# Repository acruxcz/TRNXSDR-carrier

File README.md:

# #TRNXSDR - Open RF Research Platform

**A modular baseboard designed for advanced Software Defined Radio (SDR) ecosystems.**

---

## 📝 Project Overview
The **TRNXSDR** is a hardware platform engineered to host and interconnect specialized SDR modules. It acts as the central processing hub, providing high-speed logic, memory bandwidth, and versatile connectivity for complex radio applications.

> [!IMPORTANT]
> The **TRNXSDR** is a **Baseboard Platform**. While it provides the processing power and RF routing, it requires external SDR modules connected via the expansion slots for full radio functionality.

## #TRNXSDR Baseboard

---

## Key Technical Specifications

### ⚙️ Processing & Memory
*   **FPGA XC7Z015 Core**: High-speed logic for real-time Digital Signal Processing (DSP).
*   **1 GB DDR3 RAM @ 1066 MHz**: High-capacity memory for data buffering and complex waveform processing.
*   **80-pin Module Connectors**: High-density connectors ensuring reliable signal integrity between the baseboard and modules.

### 🌐 Connectivity & I/O
*   **1 Gbit Ethernet (Copper)**: Standard high-speed network integration.
*   **Optical Ethernet (SFP)**: Hardware ready for fiber-optic connection. Planned support for **1 Gbit / 2.5 Gbit+** throughput via GTX connection (up to **5 Gbit** for custom digital IF).
*   **USB-C**: Hardware support for **Power Delivery (PD)** to power the entire board via a single cable (9–20 V input). Firmware currently under development.
*   **4 SMA RF Connectors**: On-board SMA connectors for direct and stable antenna connections.

---

## 🛠 Modular Ecosystem & Scalability
The platform is designed to grow. The baseboard features a flexible slot system to accommodate various SDR modules.

| Slot Type | Quantity | Technical Capabilities |
| :--- | :---: | :--- |
| **Primary HS Slots** | **2** | **High-Speed Support**: 1x with 2L GTX (JESD204B support), both slots support LVDS. |
| **Primary LS Slots** | **2** | **Standard I/O**: Optimized for general-purpose SDR control and low-speed buses. |
| **Expansion Board** | **+6** | **Low-Speed Expansion**: Optimized for SPI, I2C, and LVDS control buses. |

---

## 💻 Software & Integration

### GNU Radio Support (Active Development)
**Core functionality is already verified!** We have developed a custom **OOT (Out-Of-Tree) Module**, enabling basic RX streaming between the hardware and GNU Radio.
*   *Current focus*: Stability improvements, feature expansion, and bug fixes.

Below, you can see a GNU Radio Companion (GRC) flowgraph demonstrating the implementation of the dedicated #TRNXSDR source block.

### Signal Analysis & Verification
To verify the RF chain's integrity, we tested the SDR in the 433 MHz band. The following image shows the captured spectrum in GRC, displaying a clean signal peak and minimal noise floor.

Furthermore, we performed a dynamic frequency shift test. In the waterfall plot below, you can see a "snake" pattern created by manually sweeping the carrier frequency. The sweep was performed roughly within a ±500 kHz range around the 433 MHz center.

### Future Software Roadmap (Planned)
*   **SoapySDR Compatibility**: Integration of a SoapySDR driver to provide a vendor-neutral API for tools like **SDR++, SDRangel, GNU Radio and more**.
*   **OpenWiFi Project**: Investigating the possibility of hosting the OpenWiFi stack (IEEE 802.11 FPGA/Software) on #TRNXSDR hardware.

---

## #TRNXSDR with AT86RF215 SDR Module and RFFC5072 Mixer Module + RF Front-End (LNA, PA...) Module

---

## 🟢 Future Hardware Roadmap
Expanding the #TRNXSDR ecosystem with high-end RF modules:
*   **Expansion Board**: A dedicated add-on board adding **6 additional low-speed slots** (Total of 10 modules).
*   **New SDR Modules**:
    *   **Lime Ecosystem**: Modules based on **LMS6002D** and **LMS7002M** (MIMO, wide frequency range).
    *   **Analog Devices Series**: High-performance transceivers based on **AD9361 / AD9363 / AD9364**.

---

## 🛠 Development Status

- [x] **Baseboard Hardware Design**: Completed (Rev 1.0) — *Functional, with known bugs being addressed.*
- [/] **Hardware Revision 2.0**: In progress (bug fixes and optimizations).
- [/] **GNU Radio OOT Module**: Functional — *Ongoing development and feature updates.*
- [/] **Optical Port**: Hardware ready, firmware development in progress.
- [/] **USB-C Power Delivery**: Hardware support implemented, firmware under active development.
- [ ] **SoapySDR & OpenWiFi**: Conceptual/Planned stage.

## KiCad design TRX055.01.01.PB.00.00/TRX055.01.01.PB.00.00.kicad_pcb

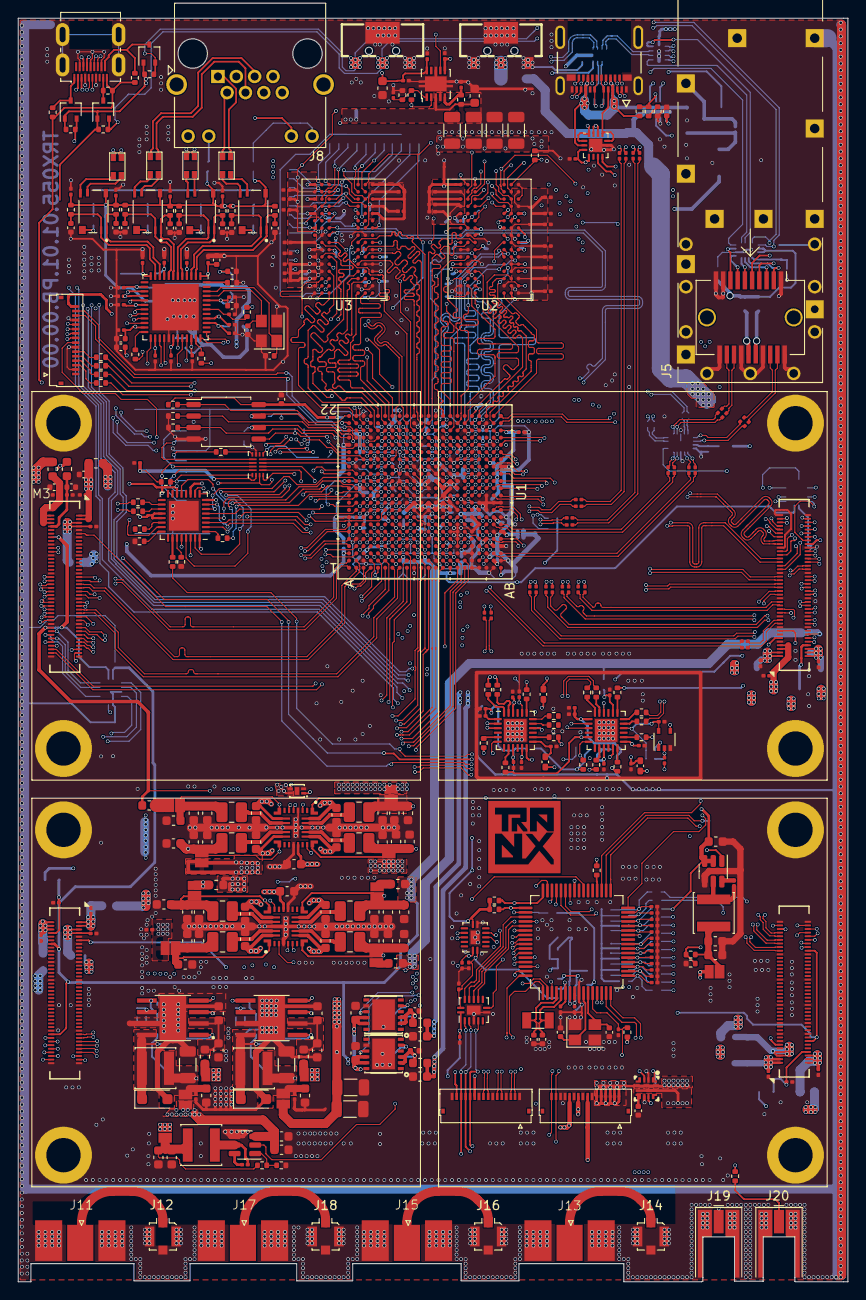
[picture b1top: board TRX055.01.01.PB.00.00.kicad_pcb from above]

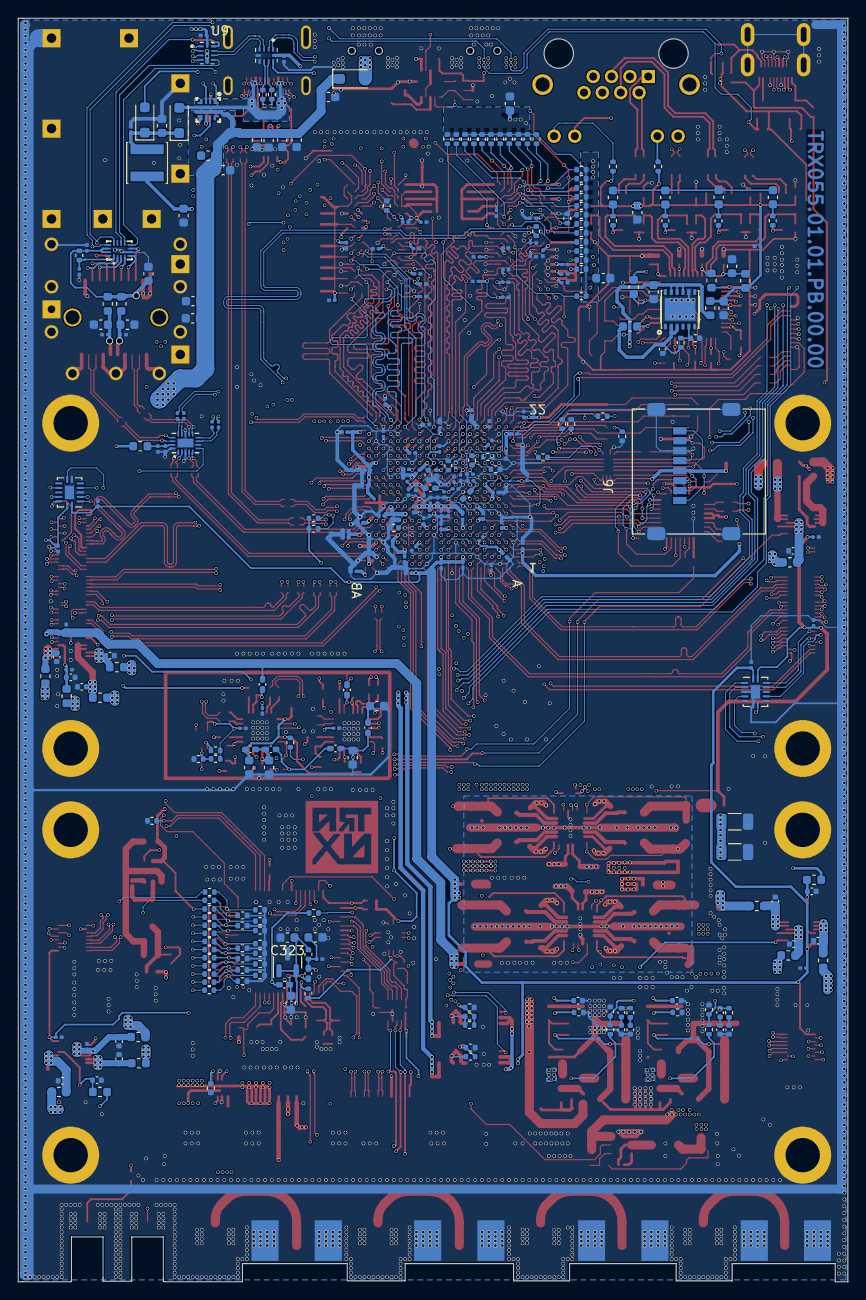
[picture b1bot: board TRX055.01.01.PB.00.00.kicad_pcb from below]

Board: 6 copper layers, 91.8 x 139.8 mm, 702 parts (313 on the bottom side), 611 nets.

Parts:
C1, C2, C3, C4, C5, C6, C7, C8, C9, C10, C11, C12, C13, C14, C15, C16, C17, C18, C19, C20, C21, C22, C23, C24, C111, C148, C149, C150, C154, C155, C156, C157, C158, C159, C160, C161, C162, C163, C164, C165, C169, C171, C174, C176, C227, C229, C231, C233, C234, C239, C245, C246, C247, C248, C249, C250, C257, C282, C283, C284, C285, C286, C288, C310, C311, C313, C314, C323, C324, C325, C326: 10M; C_0603_1608Metric
C25, C113, C114, C117, C124, C127, C186, C188, C190, C192, C194, C196, C198, C200, C202, C204, C206, C208, C210, C212, C214, C216, C240, C244, C289: 1M; C_0402_1005Metric
C26, C27, C28, C29, C30, C31, C32, C33, C34, C35, C36, C37, C38, C39, C40, C41, C42, C43, C44, C45, C46, C47, C48, C49, C50, C51, C52, C53, C54, C55, C56, C57, C58, C59, C60, C61, C62, C63, C64, C65, C66, C67, C68, C69, C70, C71, C72, C73, C74, C75, C76, C77, C78, C79, C80, C81, C82, C83, C84, C85, C86, C87, C88, C89, C90, C91, C92, C93, C94, C95, C96, C97, C98, C99, C100, C101, C102, C103, C104, C105, C106, C107, C110, C112, C115, C116, C118, C119, C120, C121, C122, C123, C125, C126, C128, C129, C130, C133, C137, C141, C145, C147, C151, C152, C153, C166, C167, C168, C170, C172, C173, C175, C177, C178, C179, C184, C185, C187, C189, C191, C193, C195, C197, C199, C201, C203, C205, C207, C209, C211, C213, C215, C217, C218, C219, C220, C221, C222, C223, C224, C225, C226, C228, C230, C232, C235, C236, C253, C258, C259, C260, C261, C262, C263, C264, C265, C266, C267, C268, C269, C270, C271, C272, C273, C274, C275, C276, C277, C278, C281, C287, C290, C291, C292, C293, C294, C295, C296, C297, C298, C299, C300, C301, C302, C303, C304, C305, C306, C307, C308, C309, C312, C315, C316, C317, C318, C319, C320, C321, C322, C327, C328, C329, C330, C331, C332, C333, C334, C335, C336, C337, C338, C339, C340, C341, C342, C343, C344, C345, C346, C347, C348, C349, C350, C351, C352, C353, C354, C355, C356, C357, C358, C359, C360, C361, C362, C363, C364, C365, C366, C367, C368, C382, C383: M1; C_0201_0603Metric
C108, C109, C131, C132, C135, C136, C139, C140, C143, C144, C180, C181, C182, C183, C237, C241, C243, C252, C254, C255: 10P; C_0402_1005Metric
C134, C138, C142, C146: 1N; C_0603_1608Metric
C238, C256, C378, C379, C380, C381, C391, C395, C396, C397: 100M; C_1206_3216Metric
C242, C251: 10N (DNP); C_0402_1005Metric
C279, C280: Cap; C_0402_1005Metric
C369, C370, C371, C372, C373, C374, C375, C376, C377: 22M; C_0603_1608Metric
D1, D2, D3, D4, D5: DSK34; D_SOD-123F
FB1, FB2, FB3, FB4, FB5, FB7, FB8, FB9, FB10, FB18, FB19, FB20, FB21, FB22, FB23, FB24, FB25, FB26, FB27, FB28, FB29, FB30, FB31, FB32, FB33, FB34, FB35, FB36, FB37, FB38, FB39, FB40: BLM18PG330SN1D; L_0603_1608Metric
FB6, FB11, FB12, FB13, FB14, FB15, FB16, FB17, FB41, FB42, FB43, FB44, FB45: GZ1005U102TF; L_0402_1005Metric_Pad0.77x0.64mm_HandSolder
J5: SFP; Connector_SFP_and_Cage
J6: Micro_SD_Card; microSD_HC_Molex_47219-2001
J7: HDMI_D_1.4; HDMI_Micro-D_Molex_46765-1x01
J8: RJHSE5383; RJ45_Amphenol_RJHSE538X
J9: 1054500101; MOLEX_1054500101
J10, J23, J24: Conn_01x16_Pin; FH34SRJ-16S-0.5SH
J11, J13, J15, J17: HYCW12-SMAW0863-1365B; sma-edge
J12, J14, J16, J18: U.FL-R-SMT-1(80); U.FL_Molex_MCRF_73412-0110_Vertical
J19, J20: Conn_Coaxial; MMCX_Molex_73415-0961_Horizontal_1.6mm-PCB
J21, J22: GT-BTP30003-0720A-016A; BAT-SMD_GT-BTP30003-0500A-016A-1
JP1, JP2, JP3, JP4, JP5, JP6, JP7, JP8, JP9, JP10, JP11, JP12, JP13, JP14: Jumper_2_Open; SolderJumper-2_P1.3mm_open_Pad1.0x1.5mm
L1, L2, L3, L4, L5, L6, L7, L8: DFE252012PD-R47M; L_1008_2520Metric
L9, L10, L11, L12: SRF2012A-801Y
L13, L15, L16, L17, L18: EXLA1V0402-4R7-R; EXLA1V04
M1, M2, M3, M4: DF40HC-80DS; module_sdr_kit_base
Q1, Q2, Q3: NTS4001NT1G; SOT-323_SC-70
R1, R2, R3, R4, R6, R8, R12, R49, R69, R70, R71, R72, R86, R88, R89, R91, R92, R93, R94, R95, R96, R97, R101, R102, R103, R104, R105, R106, R107, R108, R109, R110, R111, R112, R113, R114, R115, R116, R117, R118, R119, R120, R121, R122, R123, R124, R125, R126, R127, R128, R130, R131, R132, R133, R134, R135, R136, R142, R143, R146, R147, R148, R149, R150, R151, R153, R154, R155, R156, R157, R158, R159, R160, R161, R164, R165, R166: 10K; R_0402_1005Metric
R5, R7, R162: 5K1; R_0402_1005Metric
R9, R10, R11, R13, R15, R16, R30, R31, R32, R33, R34, R35, R36, R37, R38, R39, R40, R41, R42, R43, R44, R45, R46, R47: 39R; R_0402_1005Metric
R14, R17, R18, R19, R20, R21, R22, R23, R24, R25, R26, R27, R28, R56, R57, R73, R74, R75, R76, R77, R78, R79, R80, R81, R82, R83, R84, R85, R87, R90, R141, R144, R145, R163: 33R; R_0402_1005Metric
R29, R98: 8K06; R_0402_1005Metric
R48, R52, R53: 80R; R_0402_1005Metric
R50, R51: 240R; R_0402_1005Metric
R54: 12K1; R_0402_1005Metric
R55, R58, R60, R61, R63, R64, R66, R67: 49R9; R_0402_1005Metric
R59, R62, R65, R68: 75R; R_0402_1005Metric
R99, R100: 240; R_0402_1005Metric
R129: 100K; R_0402_1005Metric
R137, R139: 33; R_0402_1005Metric
R138, R140: NU; R_0402_1005Metric
R152: 500; R_0402_1005Metric
T1, T2, T3, T4: SM453229-231N7Y; XFMR_SM453229-231N7Y
U1: XC7Z015-2CLG485I; CLG485XC7Z012S&slash_XC7Z015_AMD
U2, U3: K4B4G1646E-BYMA; BGA-96_9.0x13.0mm_Layout2x3x16_P0.8mm
U4, U6: LP87524JRNFRQ1; VREG_LP87524JRNFRQ1
U5, U8, U31: NCP186AMN080TBG; DFN-12_L4.0-W4.0-P0.65-BL-EP3.4
U7, U34: TPS54531DDAR; CONV_TPS54531DDAR
U9, U20: TS3USB221RSER; IC_TPD6E001RSER
U10: NVT4858HKZ; XQFN16
U11: KSZ9031RNXCA; QFN-48-1EP_7x7mm_P0.5mm_EP5.15x5.15mm
U12: USB3320C-EZK-TR; QFN-32-1EP_5x5mm_P0.5mm_EP3.3x3.3mm
U13, U16: 5P35023B-000NLGI; VQFN-24-1EP_4x4mm_P0.5mm_EP2.5x2.5mm
U14: W25Q128JVSIQ; SOIC-8_5.23x5.23mm_P1.27mm
U15: TPS51200DRC; VSON-10-1EP_3x3mm_P0.5mm_EP1.65x2.4mm
U17: STM32G070RBTx; LQFP-64_10x10mm_P0.5mm
U18: TL431DBZ; SOT-23
U19, U23, U32, U33: TXU0304; DHVQFN-14-1EP_2.5x3mm_P0.5mm_EP1x1.5mm
U21, U30: AP63203WU; TSOT-23-6
U22: TCA6408ARSVR; UQFN-16_L2.6-W1.8-P0.40-BL
U24: SIP32409DNP-T1-GE4; UDFN-5_L1.6-W1.2-P0.50-BL-EP
U25: FUSB302BMPX; WQFN-14-1EP_2.5x2.5mm_P0.5mm_EP1.45x1.45mm
U26: FUSB340TMX; TMLP-18_L2.8-W2.0-P0.40-BL-EP
U27, U29: LM73100RPWR; VQFN-10_L2.0-W2.0-P0.45-TL
U28: SN74LVC1G125DCKR; SOT-353_SC-70-5
Y1, Y2: X322525MOB4SI; Crystal_SMD_3225-4Pin_3.2x2.5mm
Y3: XKXGI-SUA-32.768K; Crystal_SMD_3215-2Pin_3.2x1.5mm

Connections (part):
+1V2: C244.1, FB37.1, R5.1, U8.2 (OUT), U8.3 (OUT)
+1V8: C25.1, C26.1, C27.1, C57.1, C58.1, C59.1, C60.1, C127.1, C128.1, C129.1, C130.1, C247.1, C248.1, C293.1, FB6.1, FB43.2, J10.16, JP4.2 (B), R12.1, R69.1, R146.2, R151.2, R153.2, R155.2, R156.2, R157.1, R158.1, U1.A13 (VCCO_MIO1_501), U1.B10 (VCCO_MIO1_501), U1.B20 (VCCO_MIO0_500), U1.C17 (VCCO_MIO0_500), U1.D14 (VCCO_MIO1_501), U1.E11 (VCCO_MIO1_501), U1.K14 (VCCPAUX), U1.L13 (VCCPAUX), U1.M14 (VCCPAUX), U1.P14 (VCCPAUX), U1.R11 (VCCO_0), U5.10 (IN), U5.11 (IN), U8.10 (IN), U8.11 (IN), U10.15 (VCCA), U11.16 (DVDDH), U11.34 (DVDDH), U11.40 (DVDDH), U12.8 (REFSEL0), U12.11 (REFSEL1), U12.14 (REFSEL2), U12.28 (VDD18), U12.30 (VDD18), U12.32 (VDDIO), U14.8 (VCC), U24.1 (IN), U33.8 (OE), U33.14 (VCCB)
+3V3: C153.1, C154.1, C226.1, C231.1, C232.1, C273.1, C275.2, C276.2, C277.2, C278.2, C288.1, FB4.2, FB34.2, FB35.2, FB40.2, FB42.2, J6.4 (VDD), JP7.2 (B), Q1.1 (G), Q2.1 (G), Q3.1 (G), R95.1, R103.1, R104.1, R106.1, R154.2, U9.10 (VCC), U10.14 (VCCB), U12.20 (VDD33), U12.21 (VBAT), U12.23 (ID), U15.10 (VIN), U20.10 (VCC), U22.14 (VCCP), U22.15 (VCCI), U25.3 (VDD), U25.4 (VDD), U31.9 (EN), U31.10 (IN), U31.11 (IN)
/A1_HS1_CLK_N: M1.22, U1.AA14 (IO_L11P_T1_SRCC_13)
/A1_HS1_CLK_P: M1.20, U1.AA15 (IO_L11N_T1_SRCC_13)
/A1_HS_4_N: M1.36, U1.AA11 (IO_L7P_T1_13)
/A1_HS_4_P: M1.38, U1.AB11 (IO_L7N_T1_13)
/A1_HS_5_N: M1.35, U1.V11 (IO_L4P_T0_13)
/A1_HS_5_P: M1.37, U1.W11 (IO_L4N_T0_13)
/A1_HS_6_N: M1.40, U1.W12 (IO_L3P_T0_DQS_13)
/A1_HS_6_P: M1.42, U1.W13 (IO_L3N_T0_DQS_13)
/A1_HS_7_N: M1.39, U1.AB12 (IO_L8N_T1_13)
/A1_HS_7_P: M1.41, U1.AA12 (IO_L8P_T1_13)
/A1_HS_8_N: M1.44, U1.AB13 (IO_L9P_T1_DQS_13)
/A1_HS_8_P: M1.46, U1.AB14 (IO_L9N_T1_DQS_13)
/A1_HS_9_N: M1.43, U1.Y12 (IO_L10P_T1_13)
/A1_HS_9_P: M1.45, U1.Y13 (IO_L10N_T1_13)
/A1_HS_10_N: M1.50, U1.V15 (IO_L2P_T0_13)
/A1_HS_10_P: M1.52, U1.W15 (IO_L2N_T0_13)
/A1_HS_11_N: M1.49, U1.AA17 (IO_L14N_T2_SRCC_13)
/A1_HS_11_P: M1.51, U1.AA16 (IO_L14P_T2_SRCC_13)
/A1_HS_12_N: M1.54, U1.V16 (IO_L23P_T3_13)
/A1_HS_12_P: M1.56, U1.W16 (IO_L23N_T3_13)
/A1_HS_13_N: M1.53, U1.W17 (IO_L24P_T3_13)
/A1_HS_13_P: M1.55, U1.Y17 (IO_L24N_T3_13)
/A1_HS_14_N: M1.58, U1.AB16 (IO_L17P_T2_13)
/A1_HS_14_P: M1.60, U1.AB17 (IO_L17N_T2_13)
/A1_HS_15_N: M1.57, U1.AB21 (IO_L15P_T2_DQS_13)
/A1_HS_15_P: M1.59, U1.AB22 (IO_L15N_T2_DQS_13)
/A1_HS_16_N: M1.65, U1.AB19 (IO_L16N_T2_13)
/A1_HS_16_P: M1.63, U1.AB18 (IO_L16P_T2_13)
/A1_HS_17_N: M1.69, U1.AA20 (IO_L18N_T2_13)
/A1_HS_17_P: M1.67, U1.AA19 (IO_L18P_T2_13)
/A1_HS_18_N: M1.73, U1.V19 (IO_L20N_T3_13)
/A1_HS_18_P: M1.71, U1.U19 (IO_L20P_T3_13)
/A1_LS_GPIO_0: M1.72, U1.U12 (IO_L5N_T0_13)
/A1_LS_GPIO_1: M1.74, U1.V14 (IO_L1N_T0_13)
/A1_LS_GPIO_2: M1.76, U1.T16 (IO_0_13)
/A1_LS_GPIO_3: M1.78, U1.U16 (IO_25_13)
/A1_SPI_EN: U1.M8 (IO_L6P_T0_34), U19.8 (OE)
/A2_HS_16_N: M2.65, U1.R3 (IO_L17P_T2_34)
/A2_HS_16_P: M2.63, U1.R2 (IO_L17N_T2_34)
/A2_HS_17_N: M2.69, U1.R5 (IO_L23P_T3_34)
/A2_HS_17_P: M2.67, U1.R4 (IO_L23N_T3_34)
/A2_HS_18_N: M2.73, U1.R7 (IO_L24N_T3_34)
/A2_HS_18_P: M2.71, U1.P7 (IO_L24P_T3_34)
/A2_LS_GPIO_0: M2.72, U1.J7 (IO_L2P_T0_34)
/A2_LS_GPIO_1: M2.74, U1.N6 (IO_L19P_T3_34)
/A2_LS_GPIO_2: M2.76, U1.N5 (IO_L19N_T3_VREF_34)
/A2_LS_GPIO_3: M2.78, U1.P6 (IO_L20P_T3_34)
/A3_HS1_CLK_N: M3.22, U1.C6 (IO_L11P_T1_SRCC_35)
/A3_HS1_CLK_P: M3.20, U1.C5 (IO_L11N_T1_SRCC_35)
/A3_HS_4_N: M3.36, U1.D5 (IO_L12P_T1_MRCC_35)
/A3_HS_4_P: M3.38, U1.C4 (IO_L12N_T1_MRCC_35)
/A3_HS_5_N: M3.35, U1.E5 (IO_L5N_T0_AD9N_35)
/A3_HS_5_P: M3.37, U1.F5 (IO_L5P_T0_AD9P_35)
/A3_HS_6_N: M3.40, U1.A2 (IO_L15P_T2_DQS_AD12P_35)
/A3_HS_6_P: M3.42, U1.A1 (IO_L15N_T2_DQS_AD12N_35)
/A3_HS_7_N: M3.39, U1.B1 (IO_L18N_T2_AD13N_35)
/A3_HS_7_P: M3.41, U1.B2 (IO_L18P_T2_AD13P_35)
/A3_HS_8_N: M3.44, U1.C1 (IO_L16N_T2_35)
/A3_HS_8_P: M3.46, U1.D1 (IO_L16P_T2_35)
/A3_HS_9_N: M3.43, U1.C3 (IO_L14N_T2_AD4N_SRCC_35)
/A3_HS_9_P: M3.45, U1.D3 (IO_L14P_T2_AD4P_SRCC_35)
/A3_HS_10_N: M3.50, U1.D2 (IO_L17N_T2_AD5N_35)
/A3_HS_10_P: M3.52, U1.E2 (IO_L17P_T2_AD5P_35)
/A3_HS_11_N: M3.49, U1.E4 (IO_L21P_T3_DQS_AD14P_35)
/A3_HS_11_P: M3.51, U1.E3 (IO_L21N_T3_DQS_AD14N_35)
/A3_HS_12_N: M3.54, U1.F1 (IO_L23N_T3_35)
/A3_HS_12_P: M3.56, U1.F2 (IO_L23P_T3_35)
/A3_HS_13_N: M3.53, U1.G1 (IO_L24N_T3_AD15N_35)
/A3_HS_13_P: M3.55, U1.H1 (IO_L24P_T3_AD15P_35)
/A3_HS_14_N: M3.58, U1.F4 (IO_L20N_T3_AD6N_35)
/A3_HS_14_P: M3.60, U1.G4 (IO_L20P_T3_AD6P_35)
/A3_HS_15_N: M3.57, U1.G2 (IO_L22N_T3_AD7N_35)
/A3_HS_15_P: M3.59, U1.G3 (IO_L22P_T3_AD7P_35)
/A3_HS_16_N: M3.65, U1.H4 (IO_L19P_T3_35)
/A3_HS_16_P: M3.63, U1.H3 (IO_L19N_T3_VREF_35)
/A3_HS_17_N: M3.69, U1.G6 (IO_L6P_T0_35)
/A3_HS_17_P: M3.67, U1.F6 (IO_L6N_T0_VREF_35)
/A3_HS_18_N: M3.73, U1.G8 (IO_L4P_T0_35)
/A3_HS_18_P: M3.71, U1.G7 (IO_L4N_T0_35)
/A3_LS_GPIO_0: M3.72, U1.H6 (IO_0_35)
/A3_LS_GPIO_1: M3.74, U1.H5 (IO_25_35)
/A3_LS_GPIO_2: M3.76, U1.D7 (IO_L2P_T0_AD8P_35)
/A3_LS_GPIO_3: M3.78, U1.D6 (IO_L2N_T0_AD8N_35)
/A3_SPI_EN: U1.K8 (IO_L1N_T0_34), U23.8 (OE)
/A4_HS_16_N: M4.65, U1.L2 (IO_L10P_T1_34)
/A4_HS_16_P: M4.63, U1.L1 (IO_L10N_T1_34)
/A4_HS_17_N: M4.69, U1.M2 (IO_L15P_T2_DQS_34)
/A4_HS_17_P: M4.67, U1.M1 (IO_L15N_T2_DQS_34)
/A4_HS_18_N: M4.73, U1.P1 (IO_L16N_T2_34)
/A4_HS_18_P: M4.71, U1.N1 (IO_L16P_T2_34)
/A4_LS_GPIO_0: M4.72, U1.K2 (IO_L9N_T1_DQS_34)
/A4_LS_GPIO_1: M4.74, U1.T2 (IO_L13P_T2_MRCC_34)
/A4_LS_GPIO_2: M4.76, U1.U1 (IO_L14N_T2_SRCC_34)
/A4_LS_GPIO_3: M4.78, U1.U2 (IO_L14P_T2_SRCC_34)
/Clocking/CLK_PWR: FB13.1, FB14.1, R142.1
/Clocking/CLK_PWR_VBAT: R142.2, U13.6 (VBAT), U16.6 (VBAT)
/Clocking/CLK_REF_IN: R87.2, R90.2
/Clocking/EXT_REF_EN: R166.2, U17.41 (PD9), U28.1
/Clocking/VDD_13F: C319.1, FB44.1, U13.20 (VDDSE3)
/Clocking/VDD_18F: C318.1, FB43.1, U16.13 (VDDSE1)
/Clocking/VDD_34F: C317.1, C320.1, FB41.1, U13.13 (VDDSE1), U16.20 (VDDSE3)
/Clocking/VDD_35F: C321.1, FB45.1, U13.11 (VDDSE2)
/Clocking/VDD_DIFF: C308.1, C309.1, C315.1, C316.1, C322.1, C383.2, FB42.1, R165.1, R166.1, U13.16 (VDDDIFF1), U13.22 (VDDDIFF2), U16.11 (VDDSE2), U16.16 (VDDDIFF1), U16.22 (VDDDIFF2), U28.5 (VCC)
/ETH_PHY_Metal/ETH_Pair1/MDI_IN_N: C135.1, R60.2, T2.2, U11.8 (TXRXM_C)
/ETH_PHY_Metal/ETH_Pair1/MDI_IN_P: C136.1, R61.2, T2.1, U11.7 (TXRXP_C)
/ETH_PHY_Metal/ETH_Pair1/MDI_N: J8.5, L10.2
/ETH_PHY_Metal/ETH_Pair1/MDI_P: J8.4, L10.3
/ETH_PHY_Metal/ETH_Pair1/POE: R62.1, T2.3, T2.4
/ETH_PHY_Metal/ETH_Pair2/MDI_IN_N: C139.1, R63.2, T3.2, U11.6 (TXRXM_B)
/ETH_PHY_Metal/ETH_Pair2/MDI_IN_P: C140.1, R64.2, T3.1, U11.5 (TXRXP_B)
/ETH_PHY_Metal/ETH_Pair2/MDI_N: J8.6, L11.2
/ETH_PHY_Metal/ETH_Pair2/MDI_P: J8.3, L11.3
/ETH_PHY_Metal/ETH_Pair2/POE: R65.1, T3.3, T3.4
/ETH_PHY_Metal/ETH_Pair3/MDI_IN_N: C143.1, R66.2, T4.2, U11.3 (TXRXM_A)
/ETH_PHY_Metal/ETH_Pair3/MDI_IN_P: C144.1, R67.2, T4.1, U11.2 (TXRXP_A)
/ETH_PHY_Metal/ETH_Pair3/MDI_N: J8.2, L12.2
/ETH_PHY_Metal/ETH_Pair3/MDI_P: J8.1, L12.3
/ETH_PHY_Metal/ETH_Pair3/POE: R68.1, T4.3, T4.4
/ETH_PHY_Metal/ETH_Pair/MDI_IN_N: C131.1, R55.2, T1.2, U11.11 (TXRXM_D)
/ETH_PHY_Metal/ETH_Pair/MDI_IN_P: C132.1, R58.2, T1.1, U11.10 (TXRXP_D)
/ETH_PHY_Metal/ETH_Pair/MDI_N: J8.8, L9.2
/ETH_PHY_Metal/ETH_Pair/MDI_P: J8.7, L9.3
/ETH_PHY_Metal/ETH_Pair/POE: R59.1, T1.3, T1.4
/ETH_PHY_Metal/SMI_MDC: U1.D13 (PS_MIO52_501), U11.36 (MDC)
/ETH_PHY_Metal/SMI_MDIO: U1.C11 (PS_MIO53_501), U11.37 (MDIO)
/ETH_PHY_Metal/nLED1: J8.11, U11.17 (LED1/PHAD0/PME_N1)
/ETH_PHY_Metal/nLED2: J8.9, U11.15 (LED2/PHYAD1)
/EXTIO_CLK_N: J23.9, U1.L4 (IO_L12N_T1_MRCC_34)
/EXTIO_CLK_P: J23.8, U1.L5 (IO_L12P_T1_MRCC_34)
/EXTIO_CS: J23.15, U1.K5 (IO_L7N_T1_34)
/EXTIO_D0_N: J23.6, U1.N3 (IO_L21N_T3_DQS_34)
/EXTIO_D0_P: J23.5, U1.N4 (IO_L21P_T3_DQS_34)
/EXTIO_D1_N: J23.3, U1.P2 (IO_L18N_T2_34)
/EXTIO_D1_P: J23.2, U1.P3 (IO_L18P_T2_34)
/FCCLK: U4.3 (CLKIN), U6.3 (CLKIN), U17.39 (PC7)
/FPGA_CLK_REF_0: R77.2, R163.2, U1.T1 (IO_L13N_T2_MRCC_34), U13.5 (CLKINB/X1)
/FPGA_CLK_REF_1_N: R78.2, U1.K3 (IO_L11N_T1_SRCC_34)
/FPGA_CLK_REF_1_P: R79.2, U1.K4 (IO_L11P_T1_SRCC_34)
/GTP_REF_CLK0_N: C106.1, M1.21
/GTP_REF_CLK0_P: C104.1, M1.19
/GTP_REF_CLK1_N: C105.1, R22.2
/GTP_REF_CLK1_P: C107.1, R23.2
/GT_LANE0_SEL: U17.35 (PB15), U26.6 (S)
/GT_RX0_N: C91.1, U26.5 (SSRXCOM+)
/GT_RX0_P: C90.1, U26.4 (SSRXCOM-)
/GT_RX1_N: C89.1, C269.1
/GT_RX1_P: C88.1, C270.1
/GT_RX2_N: C93.1, M1.29
/GT_RX2_P: C92.1, M1.31
/GT_RX3_N: C95.1, M1.30
/GT_RX3_P: C94.1, M1.32
/GT_TX0_N: C97.1, U26.2 (SSTXCOM+)
/GT_TX0_P: C96.1, U26.1 (SSTXCOM-)
/GT_TX1_N: C98.1, C268.1
/GT_TX1_P: C99.1, C267.1
/GT_TX2_N: C100.1, M1.25
/GT_TX2_P: C101.1, M1.27
/GT_TX3_N: C102.1, M1.26
/GT_TX3_P: C103.1, M1.28
/HDMI/HDMI_HPD: Q3.2 (S), R106.2, U17.59 (PB5)
/MOD_A1_REFCLK: M1.11, R82.2
/MOD_A2_REFCLK: M2.11, R84.2
/MOD_A3_REFCLK: M3.11, R83.2
/MOD_A4_REFCLK: M4.11, R74.2
/Main_Power/BOOT_PWR: C286.1, C287.2, D1.1 (K), D5.1 (K), L16.1
/Main_Power/OVLO: R98.1, R99.1, U27.2 (OVLO)
/Main_Power/TPS5430DD_DCDC1/FB: R93.2, R94.1, U7.5 (VSENSE)
/Main_Power/TPS5430DD_DCDC1/TPSSW: C253.2, D3.1 (K), L13.1, U7.8 (PH)
/Main_Power/TPS5430DD_DCDC1/TPSVIN: C249.1, C250.1, FB39.2, U7.2 (VIN)
/Main_Power/TPS5430DD_DCDC1/TPSVOUT: C256.1, C257.1, C258.1, JP12.1 (A), L13.2, R93.1
/Main_Power/TPS5430DD_DCDC1/VIN: FB39.1, JP11.2 (B)
/Main_Power/TPS5430DD_DCDC/FB: R2.2, R3.1, U34.5 (VSENSE)
/Main_Power/TPS5430DD_DCDC/TPSSW: C235.2, D4.1 (K), L17.1, U34.8 (PH)
/Main_Power/TPS5430DD_DCDC/TPSVIN: C233.1, C234.1, FB36.2, U34.2 (VIN)
/Main_Power/TPS5430DD_DCDC/TPSVOUT: C236.1, C238.1, C239.1, JP9.1 (A), L17.2, R2.1
/Main_Power/TPS5430DD_DCDC/VIN: FB36.1, JP10.2 (B)
/Module_A1/MOD_SPI_MISO: M1.68, U19.10 (B4)
/Module_A1/MOD_SPI_MOSI: M1.70, U19.12 (B2Y)
/Module_A1/MOD_SPI_SCK: M1.66, U19.13 (B1Y)
/Module_A1/MOD_VDDA_5V5: C186.1, C187.1, FB18.1, M1.1, M1.3
/Module_A1/MOD_VDD_1V8D: C202.1, C203.1, FB26.1, M1.8
/Module_A1/MOD_VDD_3V3: C210.1, C211.1, FB30.1, M1.5, M1.7
/Module_A1/MOD_VDD_SYSTEM: C194.1, C195.1, FB22.1, M1.2, M1.4, M1.6
/Module_A2/MOD_VDDA_5V5: C188.1, C189.1, FB19.1, M2.1, M2.3
/Module_A2/MOD_VDD_1V8D: C204.1, C205.1, FB27.1, M2.8
/Module_A2/MOD_VDD_3V3: C212.1, C213.1, FB31.1, M2.5, M2.7
/Module_A2/MOD_VDD_SYSTEM: C196.1, C197.1, FB23.1, M2.2, M2.4, M2.6
/Module_A3/MOD_SPI_MISO: M3.68, U23.10 (B4)
/Module_A3/MOD_SPI_MOSI: M3.70, U23.12 (B2Y)
/Module_A3/MOD_SPI_SCK: M3.66, U23.13 (B1Y)
/Module_A3/MOD_VDDA_5V5: C190.1, C191.1, FB20.1, M3.1, M3.3
/Module_A3/MOD_VDD_1V8D: C206.1, C207.1, FB28.1, M3.8
/Module_A3/MOD_VDD_3V3: C214.1, C215.1, FB32.1, M3.5, M3.7
/Module_A3/MOD_VDD_SYSTEM: C198.1, C199.1, FB24.1, M3.2, M3.4, M3.6
/Module_A4/MOD_VDDA_5V5: C192.1, C193.1, FB21.1, M4.1, M4.3
/Module_A4/MOD_VDD_1V8D: C208.1, C209.1, FB29.1, M4.8
/Module_A4/MOD_VDD_3V3: C216.1, C217.1, FB33.1, M4.5, M4.7
/Module_A4/MOD_VDD_SYSTEM: C200.1, C201.1, FB25.1, M4.2, M4.4, M4.6
/PS_UART0_RX: J10.14, U1.G16 (PS_MIO10_500)
/PS_UART0_TX: J10.15, U1.B19 (PS_MIO11_500)
/PS_UART1_RX: U1.A17 (PS_MIO13_500), U33.11 (B3Y)
/PS_UART1_TX: U1.C18 (PS_MIO12_500), U33.10 (B4)
/PWR_3V3D_EN: U17.42 (PA10/NC), U21.2 (EN)
/PWR_5V5A_EN: R1.1, U17.14 (PC1), U34.3 (EN)
/PWR_CORE_EN: R91.1, U7.3 (EN), U17.13 (PC0)
/PWR_MAIN_EN: R97.1, U17.34 (PB14), U27.1 (EN/UVLO)
/PWR_MAIN_IMON: U17.32 (PB12), U27.9 (IMON)
/PWR_MAIN_PG: U17.33 (PB13), U27.3 (PG)
/PWR_MP_EN: R96.1, U17.16 (PC3), U29.1 (EN/UVLO)
/PWR_MP_IMON: U17.26 (PC5), U29.9 (IMON)
/PWR_MP_PG: U17.15 (PC2), U29.3 (PG)
/SFP_Port/MOD_DEF0: J5.6 (MOD_DEF0), U22.4 (P2)
/SFP_Port/MOD_RS: J5.7 (RATE_SELECT), U22.5 (P3)
/SFP_Port/MOD_RX_DIS: J5.8 (RX_LOS), U22.7 (P4)
/SFP_Port/MOD_TX_DIS: J5.3 (TX_DISABLE), U22.3 (P1)
/SFP_Port/MOD_TX_FAULT: J5.2 (TX_FAULT), U22.2 (P0)
/SFP_Port/SFPI_RX_N: C260.1, J5.12 (RD-)
/SFP_Port/SFPI_RX_P: C259.1, J5.13 (RD+)
/SFP_Port/SFPI_TX_N: C262.1, J5.19 (TD-)
/SFP_Port/SFPI_TX_P: C261.1, J5.18 (TD+)
/SFP_Port/SFP_RX_N: C260.2, U26.10 (SSRX1+)
/SFP_Port/SFP_RX_P: C259.2, U26.11 (SSRX1-)
/SFP_Port/SFP_TX_N: C262.2, U26.16 (SSTX1-)
/SFP_Port/SFP_TX_P: C261.2, U26.15 (SSTX1+)
/SMU/ADC1_IN0: C295.1, R111.2, R112.1, U17.17 (PA0)
/SMU/ADC1_IN1: C296.1, R113.2, R114.1, U17.18 (PA1)
/SMU/ADC1_IN2: C297.1, R115.2, R116.1, U17.19 (PA2)
/SMU/ADC1_IN3: C298.1, R117.2, R118.1, U17.20 (PA3)
/SMU/ADC1_IN4: C299.1, R119.2, R120.1, U17.21 (PA4)
/SMU/ADC1_IN5: C300.1, R121.2, R122.1, U17.22 (PA5)
/SMU/ADC1_IN6: C301.1, R123.2, R124.1, U17.23 (PA6)
/SMU/ADC1_IN7: C302.1, R125.2, R126.1, U17.24 (PA7)
/SMU/ADC1_IN8: C303.1, R127.2, R128.1, U17.27 (PB0)
/SMU/ADC1_IN9: C304.1, R129.2, R130.1, U17.28 (PB1)
/SMU/ADC1_IN10: C305.1, R131.2, R132.1, U17.29 (PB2)
/SMU/ADC1_IN11: C306.1, R133.2, R134.1, U17.30 (PB10)
/SMU/ADC1_IN15: C307.1, R135.2, R136.1, U17.31 (PB11)
/SMU/DBG_SMU_SWCLK: J10.9, U17.46 (PA14)
/SMU/DBG_SMU_SWDIO: J10.10, U17.45 (PA13)
/SMU/GPIO0: U4.20 (NRST), U6.20 (NRST), U17.2 (PC12)
/SMU/GPIO2: U15.7 (EN), U17.58 (PB4)
/SMU/GPIO3: R157.2, U1.B18 (PS_POR_B_500), U17.49 (PC9)
/SMU/GPIO4: R158.2, U1.C14 (PS_SRST_B_501), U17.48 (PC8)
/SMU/GPIO9: U8.9 (EN), U17.3 (PC13)
/SMU/GPIO10: U5.9 (EN), U17.52 (PD2)
/SMU/GPIO11: U17.47 (PA15), U24.3 (EN)
/SMU/I2C1_SCL_A: U6.5 (SCL), U16.3 (SEL_DFC/SCL_DFC1), U17.60 (PB6)
/SMU/I2C1_SCl_B: U4.6 (SDA), U13.2 (SDA_DFCO), U17.62 (PB8)
/SMU/I2C1_SDA_A: U6.6 (SDA), U16.2 (SDA_DFCO), U17.61 (PB7)
/SMU/I2C1_SDA_B: U4.5 (SCL), U13.3 (SEL_DFC/SCL_DFC1), U17.63 (PB9)
/SMU/SPI2_MISO: U17.53 (PD3), U32.10 (B4)
/SMU/SPI2_MOSI: U17.54 (PD4), U32.13 (B1Y)
/SMU/SPI2_NSS: R109.2, U17.50 (PD0), U32.11 (B3Y)
/SMU/SPI2_SCK: U17.51 (PD1), U32.12 (B2Y)
/SMU/USART2_RX: U17.56 (PD6), U33.5 (A4Y)
/SMU/USART2_TX: U17.55 (PD5), U33.4 (A3)
/SMU/USART3_RX: J10.12, U17.1 (PC11)
/SMU/USART3_TX: J10.11, U17.64 (PC10)
/SMU/VREF: C323.1, R86.1, U17.7 (VREF+), U18.1 (K), U18.2 (REF)
/SMU/nRST: C294.1, J10.8, R110.2, U17.12 (NRST)
/SMU_CS: U1.J6 (IO_L2N_T0_34), U32.8 (OE)
/SYS_I2C_SCL: J5.5 (MOD_DEF1), J22.2, J24.16, M1.77, M2.77, M3.77, M4.77, Q1.2 (S), R103.2, U17.43 (PA11/PA9), U22.12 (SCL), U25.6 (SCL)
/SYS_I2C_SDA: J5.4 (MOD_DEF2), J22.3, J24.15, M1.75, M2.75, M3.75, M4.75, Q2.2 (S), R104.2, U17.44 (PA12/PA10), U22.13 (SDA), U25.7 (SDA)
/SYS_MISO: J23.12, M2.68, M4.68, U1.J1 (IO_L8N_T1_34), U19.5 (A4Y), U23.5 (A4Y), U32.5 (A4Y)
/SYS_MOSI: J23.14, M2.70, M4.70, U1.J2 (IO_L8P_T1_34), U19.3 (A2), U23.3 (A2), U32.2 (A1)
/SYS_SCK: J23.13, M2.66, M4.66, U1.J3 (IO_L9P_T1_DQS_34), U19.2 (A1), U23.2 (A1), U32.3 (A2)
/TMDS_CLK_N: J7.14 (CK-), U1.A7 (IO_L9P_T1_DQS_AD3P_35)
/TMDS_CLK_P: J7.12 (CK+), U1.A6 (IO_L9N_T1_DQS_AD3N_35)
/TMDS_D0_N: J7.11 (D0-), U1.A5 (IO_L10P_T1_AD11P_35)
/TMDS_D0_P: J7.9 (D0+), U1.A4 (IO_L10N_T1_AD11N_35)
/TMDS_D1_N: J7.8 (D1-), U1.B7 (IO_L8P_T1_AD10P_35)
/TMDS_D1_P: J7.6 (D1+), U1.B6 (IO_L8N_T1_AD10N_35)
/TMDS_D2_N: J7.5 (D2-), U1.B4 (IO_L13P_T2_MRCC_35)
/TMDS_D2_P: J7.3 (D2+), U1.B3 (IO_L13N_T2_MRCC_35)
/ULPI_REF_CLK_24M: R75.2, U12.26 (REFCLK)
/ULPI_RESET: R89.2, U12.27 (~RESETB)
/USB_C/USBC_DM: J9.A7 (D1-), J9.B6 (D2+), R17.1
/USB_C/USBC_DP: J9.A6 (D1+), J9.B7 (D2-), R14.1
/USB_C/USB_CC1: J9.A5 (CC1), U25.10 (CC1), U25.11 (CC1)
/USB_C/USB_CC2: J9.B5 (CC2), U25.1 (CC2), U25.14 (CC2)
/USB_C/USB_IM_N: U9.7 (D_), U20.4 (2D-)
/USB_C/USB_IM_P: U9.8 (D+), U20.3 (2D+)
/USB_C/USB_RX1_N: C266.2, J9.B10 (RX1-)
/USB_C/USB_RX1_P: C264.2, J9.B11 (RX1+)
/USB_C/USB_RX2_N: C270.2, J9.A10 (RX2-)
/USB_C/USB_RX2_P: C269.2, J9.A11 (RX2+)
/USB_C/USB_TX1_N: C265.2, J9.A3 (TX1-)
/USB_C/USB_TX1_P: C263.2, J9.A2 (TX1+)
/USB_C/USB_TX2_N: C268.2, J9.B3 (TX2-)
/USB_C/USB_TX2_P: C267.2, J9.B2 (TX2+)
/USB_C/VCONN: U25.12 (VCONN), U25.13 (VCONN)
/USB_N: R28.1, U20.1 (1D+)
/USB_P: R27.1, U20.2 (1D-)
/USB_REF_CLK_N: R80.2, U9.4 (2D-)
/USB_REF_CLK_P: R81.2, U9.3 (2D+)
/USB_RX2_N: C266.1, U26.8 (SSRX2+)
/USB_RX2_P: C264.1, U26.9 (SSRX2-)
/USB_SPEC_N: M1.10, U9.1 (1D+)
/USB_SPEC_P: M1.12, U9.2 (1D-)
/USB_SW_S1: U20.9 (S), U22.8 (P5)
/USB_SW_S2: U9.9 (S), U22.10 (P7)
/USB_SW_S2_OE: U9.6 (OE), U22.9 (P6)
/USB_TX2_N: C265.1, U26.14 (SSTX2-)
/USB_TX2_P: C263.1, U26.13 (SSTX2+)
/USB_VUSB: D1.2 (A), J9.A4 (VBUS_A4), J9.A9 (VBUS_A9), J9.B4 (VBUS_B4), J9.B9 (VBUS_B9), R98.2, U25.2 (VBUS), U27.5 (IN)
/ZYNQ_Bank_112/REFCLK0_N: C106.2, U1.V9 (MGTREFCLK0N_112)
/ZYNQ_Bank_112/REFCLK0_P: C104.2, U1.U9 (MGTREFCLK0P_112)
/ZYNQ_Bank_112/REFCLK1_N: C107.2, U1.V5 (MGTREFCLK1N_112)
/ZYNQ_Bank_112/REFCLK1_P: C105.2, U1.U5 (MGTREFCLK1P_112)
/ZYNQ_Bank_112/RX0_N: C91.2, U1.AB7 (MGTPRXN0_112)
/ZYNQ_Bank_112/RX0_P: C90.2, U1.AA7 (MGTPRXP0_112)
/ZYNQ_Bank_112/RX1_N: C89.2, U1.Y8 (MGTPRXN1_112)
/ZYNQ_Bank_112/RX1_P: C88.2, U1.W8 (MGTPRXP1_112)
/ZYNQ_Bank_112/RX2_N: C93.2, U1.AB9 (MGTPRXN2_112)
/ZYNQ_Bank_112/RX2_P: C92.2, U1.AA9 (MGTPRXP2_112)
/ZYNQ_Bank_112/RX3_N: C95.2, U1.Y6 (MGTPRXN3_112)
/ZYNQ_Bank_112/RX3_P: C94.2, U1.W6 (MGTPRXP3_112)
/ZYNQ_Bank_112/TX0_N: C97.2, U1.AB3 (MGTPTXN0_112)
/ZYNQ_Bank_112/TX0_P: C96.2, U1.AA3 (MGTPTXP0_112)
/ZYNQ_Bank_112/TX1_N: C98.2, U1.Y4 (MGTPTXN1_112)
/ZYNQ_Bank_112/TX1_P: C99.2, U1.W4 (MGTPTXP1_112)
/ZYNQ_Bank_112/TX2_N: C100.2, U1.AB5 (MGTPTXN2_112)
/ZYNQ_Bank_112/TX2_P: C101.2, U1.AA5 (MGTPTXP2_112)
/ZYNQ_Bank_112/TX3_N: C102.2, U1.Y2 (MGTPTXN3_112)
/ZYNQ_Bank_112/TX3_P: C103.2, U1.W2 (MGTPTXP3_112)
/ZYNQ_REF_CLK: R76.2, R159.2, U1.F16 (PS_CLK_500)
/ZynqConfig/JTAG_TCK: R18.1, U1.H11 (TCK_0)
/ZynqConfig/JTAG_TDI: R20.1, U1.H9 (TDI_0)
/ZynqConfig/JTAG_TDO: R21.1, U1.G9 (TDO_0)
/ZynqConfig/JTAG_TMS: R19.1, U1.H10 (TMS_0)
/ZynqDDR/DDR_A0: R41.1, U1.M19 (PS_DDR_A0_502), U2.N3 (A0), U3.N3 (A0)
/ZynqDDR/DDR_A1: R35.1, U1.M18 (PS_DDR_A1_502), U2.P7 (A1), U3.P7 (A1)
/ZynqDDR/DDR_A2: R11.1, U1.K19 (PS_DDR_A2_502), U2.P3 (A2), U3.P3 (A2)
/ZynqDDR/DDR_A3: R40.1, U1.L19 (PS_DDR_A3_502), U2.N2 (A3), U3.N2 (A3)
/ZynqDDR/DDR_A4: R36.1, U1.K17 (PS_DDR_A4_502), U2.P8 (A4), U3.P8 (A4)
/ZynqDDR/DDR_A5: R33.1, U1.K18 (PS_DDR_A5_502), U2.P2 (A5), U3.P2 (A5)
/ZynqDDR/DDR_A6: R30.1, U1.J16 (PS_DDR_A6_502), U2.R8 (A6), U3.R8 (A6)
/ZynqDDR/DDR_A7: R38.1, U1.J17 (PS_DDR_A7_502), U2.R2 (A7), U3.R2 (A7)
/ZynqDDR/DDR_A8: R16.1, U1.J18 (PS_DDR_A8_502), U2.T8 (A8), U3.T8 (A8)
/ZynqDDR/DDR_A9: R37.1, U1.H18 (PS_DDR_A9_502), U2.R3 (A9), U3.R3 (A9)
/ZynqDDR/DDR_A10: R10.1, U1.J20 (PS_DDR_A10_502), U2.L7 (A10/AP), U3.L7 (A10/AP)
/ZynqDDR/DDR_A11: R31.1, U1.G18 (PS_DDR_A11_502), U2.R7 (A11), U3.R7 (A11)
/ZynqDDR/DDR_A12: R13.1, U1.H19 (PS_DDR_A12_502), U2.N7 (A12/~BC), U3.N7 (A12/~BC)
/ZynqDDR/DDR_A13: R32.1, U1.F19 (PS_DDR_A13_502), U2.T3 (A13), U3.T3 (A13)
/ZynqDDR/DDR_A14: R34.1, U1.G19 (PS_DDR_A14_502), U2.T7 (A14), U3.T7 (A14)
/ZynqDDR/DDR_BA0: R39.1, U1.L16 (PS_DDR_BA0_502), U2.M2 (BA0), U3.M2 (BA0)
/ZynqDDR/DDR_BA1: R15.1, U1.L17 (PS_DDR_BA1_502), U2.N8 (BA1), U3.N8 (BA1)
/ZynqDDR/DDR_BA2: R47.1, U1.M17 (PS_DDR_BA2_502), U2.M3 (BA2), U3.M3 (BA2)
/ZynqDDR/DDR_CAS: R9.1, U1.P20 (PS_DDR_CAS_B_502), U2.K3 (~CAS), U3.K3 (~CAS)
/ZynqDDR/DDR_CK_E: R42.1, U1.T19 (PS_DDR_CKE_502), U2.K9 (CKE), U3.K9 (CKE)
/ZynqDDR/DDR_CK_N: R48.1, U1.N18 (PS_DDR_CKN_502), U2.K7 (~CK), U3.K7 (~CK)
/ZynqDDR/DDR_CK_P: R48.2, U1.N19 (PS_DDR_CKP_502), U2.J7 (CK), U3.J7 (CK)
/ZynqDDR/DDR_CS: R44.1, U1.P17 (PS_DDR_CS_B_502), U2.L2 (~CS), U3.L2 (~CS)
/ZynqDDR/DDR_DM0: U1.B22 (PS_DDR_DM0_502), U3.D3 (UDM)
/ZynqDDR/DDR_DM1: U1.H20 (PS_DDR_DM1_502), U3.E7 (LDM)
/ZynqDDR/DDR_DM2: U1.P22 (PS_DDR_DM2_502), U2.E7 (LDM)
/ZynqDDR/DDR_DM3: U1.AA21 (PS_DDR_DM3_502), U2.D3 (UDM)
/ZynqDDR/DDR_DQ0: U1.D22 (PS_DDR_DQ0_502), U3.D7 (DQ8)
/ZynqDDR/DDR_DQ1: U1.C20 (PS_DDR_DQ1_502), U3.C8 (DQ10)
/ZynqDDR/DDR_DQ2: U1.B21 (PS_DDR_DQ2_502), U3.A7 (DQ12)
/ZynqDDR/DDR_DQ3: U1.D20 (PS_DDR_DQ3_502), U3.B8 (DQ14)
/ZynqDDR/DDR_DQ4: U1.E20 (PS_DDR_DQ4_502), U3.C3 (DQ9)
/ZynqDDR/DDR_DQ5: U1.E22 (PS_DDR_DQ5_502), U3.C2 (DQ11)
/ZynqDDR/DDR_DQ6: U1.F21 (PS_DDR_DQ6_502), U3.A3 (DQ15)
/ZynqDDR/DDR_DQ7: U1.F22 (PS_DDR_DQ7_502), U3.A2 (DQ13)
/ZynqDDR/DDR_DQ8: U1.G21 (PS_DDR_DQ8_502), U3.F7 (DQ1)
/ZynqDDR/DDR_DQ9: U1.G22 (PS_DDR_DQ9_502), U3.F8 (DQ3)
/ZynqDDR/DDR_DQ10: U1.L22 (PS_DDR_DQ10_502), U3.G2 (DQ6)
/ZynqDDR/DDR_DQ11: U1.L21 (PS_DDR_DQ11_502), U3.F2 (DQ2)
/ZynqDDR/DDR_DQ12: U1.L20 (PS_DDR_DQ12_502), U3.H3 (DQ4)
/ZynqDDR/DDR_DQ13: U1.K22 (PS_DDR_DQ13_502), U3.E3 (DQ0)
/ZynqDDR/DDR_DQ14: U1.J22 (PS_DDR_DQ14_502), U3.H8 (DQ5)
/ZynqDDR/DDR_DQ15: U1.K20 (PS_DDR_DQ15_502), U3.H7 (DQ7)
/ZynqDDR/DDR_DQ16: U1.M22 (PS_DDR_DQ16_502), U2.H7 (DQ7)
/ZynqDDR/DDR_DQ17: U1.T20 (PS_DDR_DQ17_502), U2.F2 (DQ2)
/ZynqDDR/DDR_DQ18: U1.N20 (PS_DDR_DQ18_502), U2.F7 (DQ1)
/ZynqDDR/DDR_DQ19: U1.T22 (PS_DDR_DQ19_502), U2.G2 (DQ6)
/ZynqDDR/DDR_DQ20: U1.R20 (PS_DDR_DQ20_502), U2.H3 (DQ4)
/ZynqDDR/DDR_DQ21: U1.T21 (PS_DDR_DQ21_502), U2.E3 (DQ0)
/ZynqDDR/DDR_DQ22: U1.M21 (PS_DDR_DQ22_502), U2.H8 (DQ5)
/ZynqDDR/DDR_DQ23: U1.R22 (PS_DDR_DQ23_502), U2.F8 (DQ3)
/ZynqDDR/DDR_DQ24: U1.Y20 (PS_DDR_DQ24_502), U2.A2 (DQ13)
/ZynqDDR/DDR_DQ25: U1.U22 (PS_DDR_DQ25_502), U2.B8 (DQ14)
/ZynqDDR/DDR_DQ26: U1.AA22 (PS_DDR_DQ26_502), U2.A3 (DQ15)
/ZynqDDR/DDR_DQ27: U1.U21 (PS_DDR_DQ27_502), U2.D7 (DQ8)
/ZynqDDR/DDR_DQ28: U1.W22 (PS_DDR_DQ28_502), U2.C2 (DQ11)
/ZynqDDR/DDR_DQ29: U1.W20 (PS_DDR_DQ29_502), U2.A7 (DQ12)
/ZynqDDR/DDR_DQ30: U1.V20 (PS_DDR_DQ30_502), U2.C8 (DQ10)
/ZynqDDR/DDR_DQ31: U1.Y22 (PS_DDR_DQ31_502), U2.C3 (DQ9)
/ZynqDDR/DDR_DQS0_N: U1.D21 (PS_DDR_DQS_N0_502), U3.B7 (~UDQS)
/ZynqDDR/DDR_DQS0_P: U1.C21 (PS_DDR_DQS_P0_502), U3.C7 (UDQS)
/ZynqDDR/DDR_DQS1_N: U1.J21 (PS_DDR_DQS_N1_502), U3.G3 (~LDQS)
/ZynqDDR/DDR_DQS1_P: U1.H21 (PS_DDR_DQS_P1_502), U3.F3 (LDQS)
/ZynqDDR/DDR_DQS2_N: U1.P21 (PS_DDR_DQS_N2_502), U2.G3 (~LDQS)
/ZynqDDR/DDR_DQS2_P: U1.N21 (PS_DDR_DQS_P2_502), U2.F3 (LDQS)
/ZynqDDR/DDR_DQS3_N: U1.W21 (PS_DDR_DQS_N3_502), U2.B7 (~UDQS)
/ZynqDDR/DDR_DQS3_P: U1.V21 (PS_DDR_DQS_P3_502), U2.C7 (UDQS)
/ZynqDDR/DDR_ODT: R46.1, U1.P18 (PS_DDR_ODT_502), U2.K1 (ODT), U3.K1 (ODT)
/ZynqDDR/DDR_RAS: R43.1, U1.R18 (PS_DDR_RAS_B_502), U2.J3 (~RAS), U3.J3 (~RAS)
/ZynqDDR/DDR_RST: R49.1, U1.F20 (PS_DDR_DRST_B_502), U2.T2 (~RESET), U3.T2 (~RESET)
/ZynqDDR/DDR_WE: R45.1, U1.R19 (PS_DDR_WE_B_502), U2.L3 (~WE), U3.L3 (~WE)
/ZynqPower/1V5_RAIL_A: FB7.1, JP8.2 (B)
/ZynqPower/DDRVREF: U1.H16 (PS_DDR_VREF0_502), U1.P16 (PS_DDR_VREF1_502)
/ZynqPower/MGTAVCC: C45.1, C46.1, C47.1, C48.1, C49.1, C245.1, FB38.2, U1.U4 (MGTAVCC), U1.U6 (MGTAVCC), U1.U8 (MGTAVCC), U1.W5 (MGTAVCC), U1.W9 (MGTAVCC)
/ZynqPower/MGTAVTT: C40.1, C41.1, C42.1, C43.1, C44.1, C246.1, FB37.2, U1.AA2 (MGTAVTT), U1.AA4 (MGTAVTT), U1.AA8 (MGTAVTT), U1.AB1 (MGTAVTT), U1.AB6 (MGTAVTT), U1.Y7 (MGTAVTT)
/ZynqPower/PS_MIO_VREF_501: R69.2, R70.1, U1.F15 (PS_MIO_VREF_501)
/ZynqPower/QBUCK_LP87524J1/SW0: L5.1, U6.10 (SW_B0)
/ZynqPower/QBUCK_LP87524J1/SW1: L6.1, U6.12 (SW_B1)
/ZynqPower/QBUCK_LP87524J1/SW2: L7.1, U6.25 (SW_B2)
/ZynqPower/QBUCK_LP87524J1/SW3: L8.1, U6.23 (SW_B3)
/ZynqPower/QBUCK_LP87524J/SW0: L1.1, U4.10 (SW_B0)
/ZynqPower/QBUCK_LP87524J/SW1: L2.1, U4.12 (SW_B1)
/ZynqPower/QBUCK_LP87524J/SW2: L3.1, U4.25 (SW_B2)
/ZynqPower/QBUCK_LP87524J/SW3: L4.1, U4.23 (SW_B3)
/ZynqPower/VCCADC: C184.1, C185.1, FB11.2, U1.K12 (VCCADC_0)
/ZynqPower/VCCAUX: C36.1, C37.1, C38.1, C39.1, FB11.1, U1.N13 (VCCAUX), U1.P12 (VCCAUX), U1.R13 (VCCAUX), U1.T12 (VCCAUX), U24.4 (OUT)
/ZynqPower/VCCO_RAIL_A: FB9.1, JP5.2 (B)
/ZynqPower/VCCO_RAIL_B: FB8.1, JP6.2 (B)
/ZynqPower/VCCO_RAIL_C: FB10.1, JP1.2 (B)
/ZynqPower/VCCPLL: C50.1, FB6.2, U1.G13 (VCCPLL)
/Zynq_PSMIO/MIO_QSPI_CS: R151.1, U1.A22 (PS_MIO1_500), U14.1 (~CS)
/Zynq_PSMIO/MIO_QSPI_FB: R153.1, U1.D18 (PS_MIO7_500), U1.E18 (PS_MIO8_500)
/Zynq_PSMIO/MIO_QSPI_IO0: R149.2, U1.A21 (PS_MIO2_500), U14.5 (DI(IO0))
/Zynq_PSMIO/MIO_QSPI_IO1: R148.2, U1.F17 (PS_MIO3_500), U14.2 (DO(IO1))
/Zynq_PSMIO/MIO_QSPI_IO2: R147.2, U1.E19 (PS_MIO4_500), U14.3 (IO2)
/Zynq_PSMIO/MIO_QSPI_IO3: R146.1, U1.A20 (PS_MIO5_500), U14.7 (IO3)
/Zynq_PSMIO/MIO_QSPI_SCLK: R150.2, U1.A19 (PS_MIO6_500), U14.6 (CLK)
/Zynq_PSMIO/MIO_RGMII_RX0: U1.F9 (PS_MIO35_501), U11.32 (RXD0/MODE0)
/Zynq_PSMIO/MIO_RGMII_RX1: U1.A14 (PS_MIO36_501), U11.31 (RXD1/MODE1)
/Zynq_PSMIO/MIO_RGMII_RX2: U1.B9 (PS_MIO37_501), U11.28 (RXD2/MODE2)
/Zynq_PSMIO/MIO_RGMII_RX3: U1.F10 (PS_MIO38_501), U11.27 (RXD3/MODE3)
/Zynq_PSMIO/MIO_RGMII_RX_CLK: R56.1, U1.B11 (PS_MIO34_501)
/Zynq_PSMIO/MIO_RGMII_RX_CTL: U1.C10 (PS_MIO39_501), U11.33 (RX_DV/CLK125_EN)
/Zynq_PSMIO/MIO_RGMII_TX0: U1.E15 (PS_MIO29_501), U11.19 (TXD0)
/Zynq_PSMIO/MIO_RGMII_TX1: U1.A12 (PS_MIO30_501), U11.20 (TXD1)
/Zynq_PSMIO/MIO_RGMII_TX2: U1.F14 (PS_MIO31_501), U11.21 (TXD2)
/Zynq_PSMIO/MIO_RGMII_TX3: U1.C16 (PS_MIO32_501), U11.22 (TXD3)
/Zynq_PSMIO/MIO_RGMII_TX_CLK: R57.1, U1.A11 (PS_MIO28_501)
/Zynq_PSMIO/MIO_RGMII_TX_CTL: U1.G11 (PS_MIO33_501), U11.25 (TX_EN)
/Zynq_PSMIO/MIO_SD_CLK: R145.2, U1.D17 (PS_MIO16_501)
/Zynq_PSMIO/MIO_SD_CMD: U1.E14 (PS_MIO17_501), U10.16 (CMDA)
/Zynq_PSMIO/MIO_SD_D0: U1.A16 (PS_MIO18_501), U10.4 (DAT1A)
/Zynq_PSMIO/MIO_SD_D1: U1.E13 (PS_MIO19_501), U10.2 (DAT3A)
/Zynq_PSMIO/MIO_SD_D2: U1.A15 (PS_MIO20_501), U10.3 (DAT0A)
/Zynq_PSMIO/MIO_SD_D3: U1.F12 (PS_MIO21_501), U10.1 (DAT2A)
/Zynq_PSMIO/MIO_ULPI_CLK: R26.2, U1.D12 (PS_MIO48_501)
/Zynq_PSMIO/MIO_ULPI_D0: U1.E10 (PS_MIO44_501), U12.3 (DATA0)
/Zynq_PSMIO/MIO_ULPI_D1: U1.B14 (PS_MIO45_501), U12.4 (DATA1)
/Zynq_PSMIO/MIO_ULPI_D2: U1.D11 (PS_MIO46_501), U12.5 (DATA2)
/Zynq_PSMIO/MIO_ULPI_D3: U1.B13 (PS_MIO47_501), U12.6 (DATA3)
/Zynq_PSMIO/MIO_ULPI_D4: U1.E9 (PS_MIO40_501), U12.7 (DATA4)
/Zynq_PSMIO/MIO_ULPI_D5: U1.C9 (PS_MIO49_501), U12.9 (DATA5)
/Zynq_PSMIO/MIO_ULPI_D6: U1.D10 (PS_MIO50_501), U12.10 (DATA6)
/Zynq_PSMIO/MIO_ULPI_D7: U1.C13 (PS_MIO51_501), U12.13 (DATA7)
/Zynq_PSMIO/MIO_ULPI_DIR: U1.C15 (PS_MIO41_501), U12.31 (DIR)
/Zynq_PSMIO/MIO_ULPI_NXT: U1.B12 (PS_MIO43_501), U12.2 (NXT)
/Zynq_PSMIO/MIO_ULPI_STP: U1.D15 (PS_MIO42_501), U12.29 (STP)
AVDDH: C124.1, C125.1, C126.1, C325.1, FB3.1, U11.1 (AVDDH), U11.12 (AVDDH)
AVDDL: C114.1, C115.1, C116.1, FB1.1, FB5.2, U11.4 (AVDDL), U11.9 (AVDDL)
AVDDL_PLL: C112.1, C113.1, FB5.1, U11.44 (AVDDL_PLL)
DVDDL: C117.1, C118.1, C119.1, C120.1, C121.1, C122.1, C123.1, FB1.2, FB2.1, U11.14 (DVDDL), U11.18 (DVDDL), U11.23 (DVDDL), U11.26 (DVDDL), U11.30 (DVDDL), U11.39 (DVDDL)
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
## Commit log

2025-09-04 Inital commit
2025-09-11 Update Layout
2025-09-23 V0.2
2025-09-29 +ETH +USB +Connectors
2025-10-16 + add clocks + add PSU
2026-01-23 Producing - rev0.0
2026-02-10 V0.1 - production, added brig-up comments
2026-03-05 Licence update
2026-03-06 readme update
2026-03-19 Added images of SDR baseboard.
2026-03-19 Change image name
2026-03-19 Update README.md, Images, more info
2026-03-19 Update, SoapySDR, GNU Radio README.md
2026-03-23 Added GNU Radio Images.
2026-03-23 Update README.md with GNU Radio informations.
